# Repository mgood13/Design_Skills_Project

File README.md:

# Design_Skills_Project
Repository for the First Semester Design Project

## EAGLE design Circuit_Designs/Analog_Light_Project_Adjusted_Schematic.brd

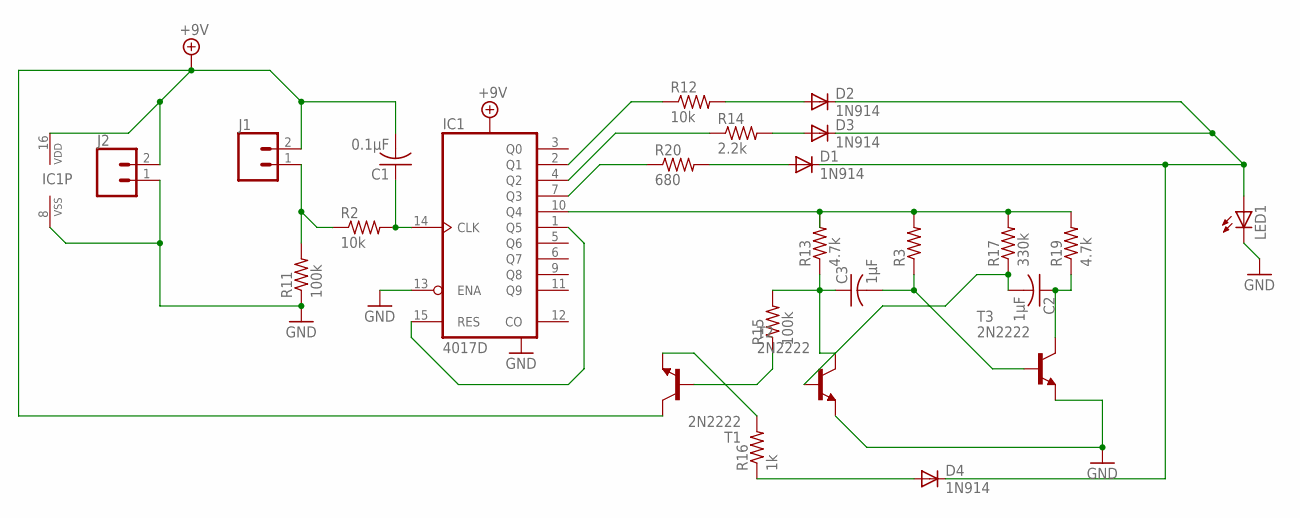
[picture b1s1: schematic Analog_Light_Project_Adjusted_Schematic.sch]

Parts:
C1: 0.1µF; C025-024X044
C2: 1µF; C0805
C3: 1µF; C025-024X044
D1, D2, D3, D4: 1N914; DO41-10
IC1: 4017D; SO16
J1, J2: CONN_02; 1X02
LED1: LED5MM
R2: 10k; 0204/5
R3: R-US_0204/5; 0204/5
R11, R15: 100k; M0805
R12: 10k; M0805
R13, R19: 4.7k; M0805
R14: 2.2k; M0805
R16: 1k; M0805
R17: 330k; M0805
R20: 680; M0805
T1, T2, T3: 2N2222; TO92-EBC-OVAL

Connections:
+9V: C1.2, IC1.16 (VDD), J1.2, J2.2, T1.C
GND: IC1.8 (VSS), IC1.13 (ENA), J2.1, LED1.K (C), R11.1, T2.E, T3.E
unnamed: IC1.10 (Q4), R3.2, R13.2, R17.2, R19.2
unnamed: C3.1, R13.1, R15.2, T2.C
unnamed: C3.2, R3.1, T3.B
unnamed: C2.2, R17.1, T2.B
unnamed: C2.1, R19.1, T3.C
unnamed: IC1.7 (Q3), R20.1
unnamed: R15.1, T1.B
unnamed: D1.C, D2.C, D3.C, D4.C, LED1.A
unnamed: IC1.4 (Q2), R14.1
unnamed: IC1.2 (Q1), R12.1
unnamed: C1.1, IC1.14 (CLK), R2.2
unnamed: IC1.1 (Q5), IC1.15 (RES)
unnamed: D1.A, R20.2
unnamed: J1.1, R2.1, R11.2
unnamed: D3.A, R14.2
unnamed: D2.A, R12.2
unnamed: D4.A, R16.1
unnamed: R16.2, T1.E

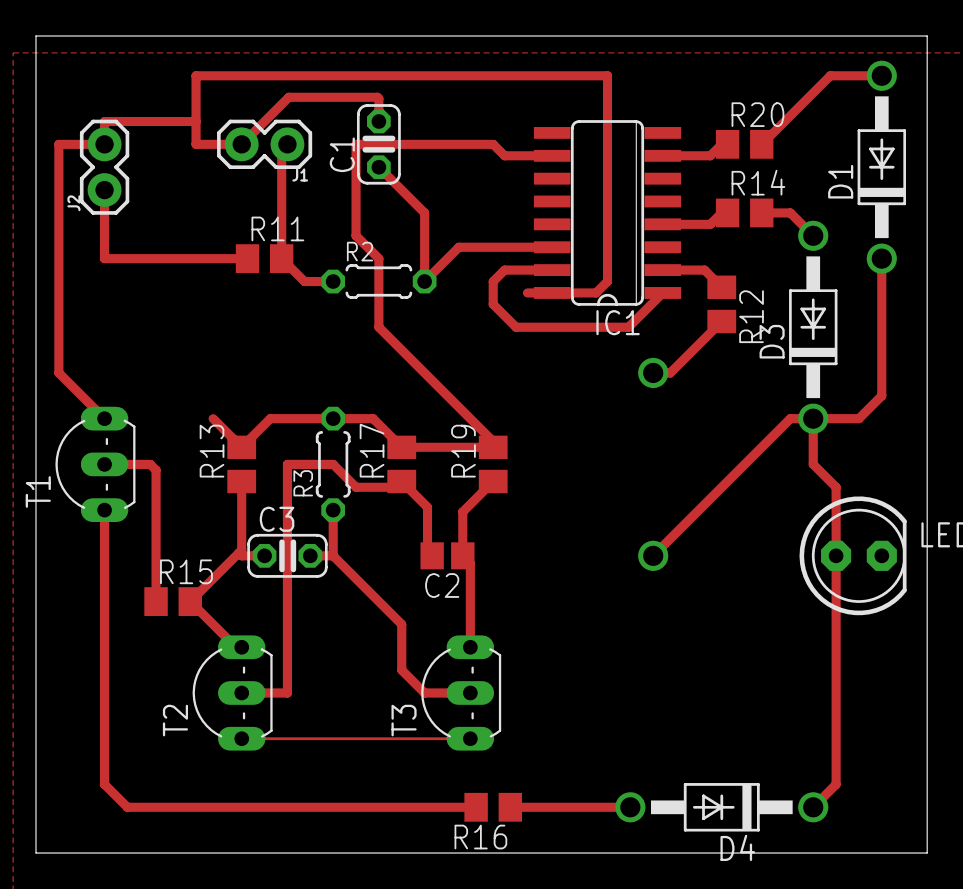
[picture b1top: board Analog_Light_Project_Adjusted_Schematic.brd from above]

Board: 2 copper layers, 49.5 x 45.4 mm, 25 parts (1 on the bottom side), 20 nets.

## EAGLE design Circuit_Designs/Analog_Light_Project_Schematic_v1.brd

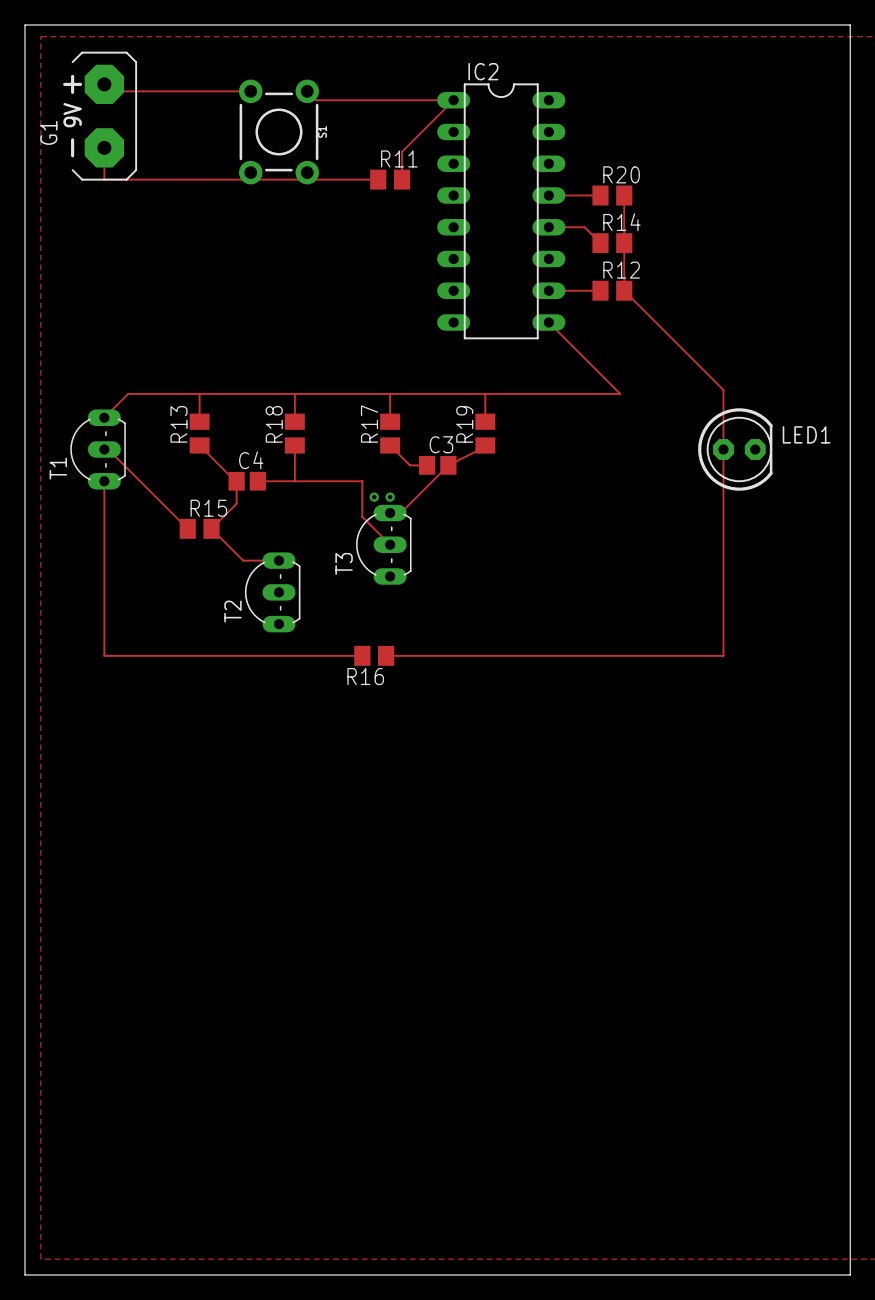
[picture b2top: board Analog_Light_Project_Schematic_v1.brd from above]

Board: 2 copper layers, 66.0 x 100.0 mm, 19 parts (0 on the bottom side), 15 nets.

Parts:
C3, C4: C0805
G1: AB9V
IC2: 4026N; DIL16
LED1: LED5MM
R11, R12, R13, R14, R15, R16, R17, R18, R19, R20: M0805
S1: MOMENTARY-SWITCH-SPST-PTH-6.0MM-KIT; TACTILE_SWITCH_PTH_6.0MM_KIT
T1, T2, T3: 2N2222; TO92-EBC-OVAL

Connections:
GND: G1.-, LED1.K, R11.1, T2.E, T3.E
unnamed: IC2.9, R13.2, R17.2, R18.2, R19.2, T1.C
unnamed: C4.1, R13.1, R15.2, T2.C
unnamed: C4.2, R18.1, T3.B
unnamed: C3.1, R17.1, T2.B
unnamed: C3.2, R19.1, T3.C
unnamed: R15.1, T1.B
unnamed: R16.2, T1.E
unnamed: LED1.A, R12.2, R14.2, R16.1, R20.2
unnamed: IC2.10, R12.1
unnamed: IC2.12, R14.1
unnamed: IC2.13, R20.1
unnamed: IC2.11, IC2.15
unnamed: G1.+, S1.3
unnamed: IC2.1, R11.2, S1.1

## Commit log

2018-10-02 Initializing the directories for the two distinct parts of the project.
2018-10-02 Updating the mechanical design ideas
2018-11-01 Adding in the diagrams from Milestone 2 and the Software Flow Diagram
2018-11-01 I have committed a cardinal sin of version control... and wrote it all in one go before commiting...
2018-11-01 Uploading Circuit diagram drawing
2018-11-05 For some reason the circuit didn't make it up to github.
2018-11-05 Adding in the analog circuit
2018-11-05 Adding in a first attempt at the schematic on EAGLE
2018-11-08 The pdf versions of the schematic and the board
2018-11-19 Adding the Mechanical CAD files
2018-11-22 Finally adding in the top with the attachment mechanism
2018-11-24 Adding in the improved versions of the case pieces
2018-11-26 Fixed the PCB with the correct parts
2018-11-28 Added the Correct schematics
2018-11-28 Improved PCB to be single-side
2018-11-28 Fixed the last 20mil files
2018-12-14 Adding in the most updated design for the bottom of the case
2018-12-14 Adding a folder containing all the old circtui designs
2018-12-14 Changed the wiring of one transistor

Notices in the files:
parts and their libraries:
SparkFun-Connectors: Licensing: Creative Commons ShareAlike 4.0 International - https://creativecommons.org/licenses/by-sa/4.0
